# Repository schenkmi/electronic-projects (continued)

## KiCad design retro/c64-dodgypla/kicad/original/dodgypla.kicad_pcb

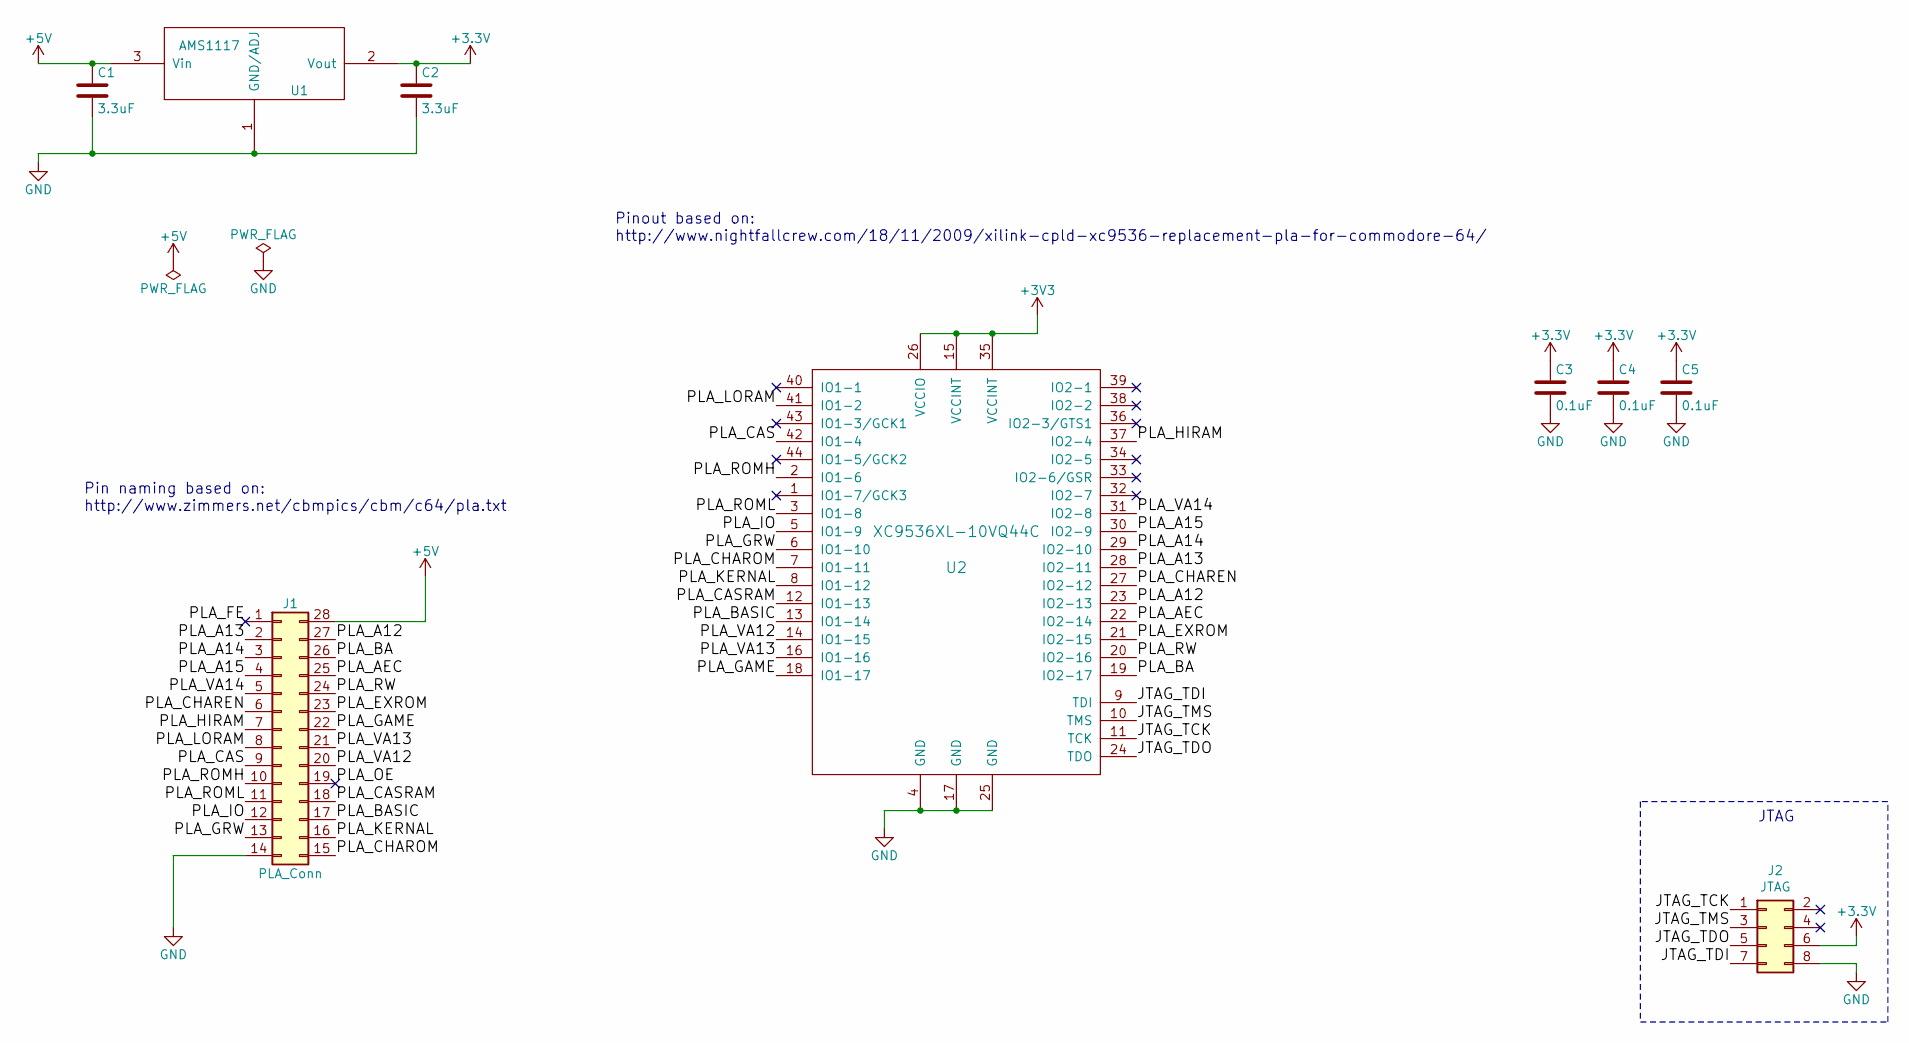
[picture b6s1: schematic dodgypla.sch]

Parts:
C1, C2: 3.3uF; C_0805
C3, C4, C5: 0.1uF; C_0805
J1: PLA_Conn; DIP-28_W15.24mm_Socket
J2: JTAG; Pin_Header_Straight_2x04_Pitch2.54mm
U1: AMS1117; SOT-223-3_TabPin2
U2: XC9536XL-10VQ44C; LQFP-44_10x10mm_P0.8mm

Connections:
+5V: C1.1, J1.28, U1.3 (Vin)
/JTAG_TCK: J2.1, U2.11 (TCK)
/JTAG_TDI: J2.7, U2.9 (TDI)
/JTAG_TDO: J2.5, U2.24 (TDO)
/JTAG_TMS: J2.3, U2.10 (TMS)
/PLA_A12: J1.27, U2.23 (IO2-13)
/PLA_A13: J1.2, U2.28 (IO2-11)
/PLA_A14: J1.3, U2.29 (IO2-10)
/PLA_A15: J1.4, U2.30 (IO2-9)
/PLA_AEC: J1.25, U2.22 (IO2-14)
/PLA_BA: J1.26, U2.19 (IO2-17)
/PLA_BASIC: J1.17, U2.13 (IO1-14)
/PLA_CAS: J1.9, U2.42 (IO1-4)
/PLA_CASRAM: J1.18, U2.12 (IO1-13)
/PLA_CHAREN: J1.6, U2.27 (IO2-12)
/PLA_CHAROM: J1.15, U2.7 (IO1-11)
/PLA_EXROM: J1.23, U2.21 (IO2-15)
/PLA_FE: J1.1
/PLA_GAME: J1.22, U2.18 (IO1-17)
/PLA_GRW: J1.13, U2.6 (IO1-10)
/PLA_HIRAM: J1.7, U2.37 (IO2-4)
/PLA_IO: J1.12, U2.5 (IO1-9)
/PLA_KERNAL: J1.16, U2.8 (IO1-12)
/PLA_LORAM: J1.8, U2.41 (IO1-2)
/PLA_OE: J1.19
/PLA_ROMH: J1.10, U2.2 (IO1-6)
/PLA_ROML: J1.11, U2.3 (IO1-8)
/PLA_RW: J1.24, U2.20 (IO2-16)
/PLA_VA12: J1.20, U2.14 (IO1-15)
/PLA_VA13: J1.21, U2.16 (IO1-16)
/PLA_VA14: J1.5, U2.31 (IO2-8)
GND: C1.2, C2.2, C3.2, C4.2, C5.2, J1.14, J2.8, U1.1 (GND/ADJ), U2.4 (GND), U2.17 (GND), U2.25 (GND)

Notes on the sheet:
Pin naming based on: http://www.zimmers.net/cbmpics/cbm/c64/pla.txt
Pinout based on: http://www.nightfallcrew.com/18/11/2009/xilink-cpld-xc9536-replacement-pla-for-commodore-64/
JTAG

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
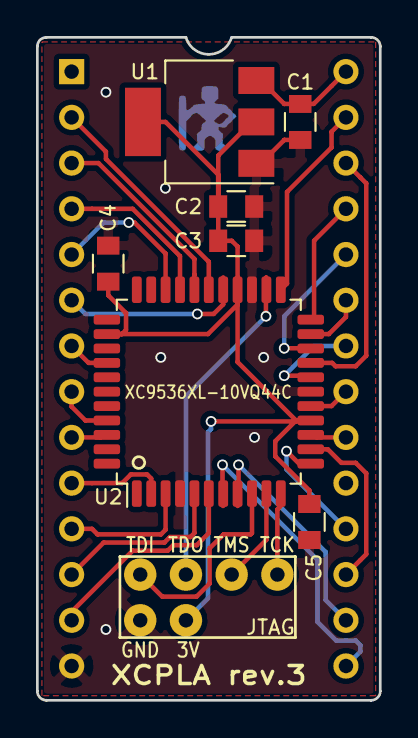
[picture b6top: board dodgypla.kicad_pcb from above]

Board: 2 copper layers, 19.0 x 36.8 mm, 9 parts (0 on the bottom side), 31 nets.
